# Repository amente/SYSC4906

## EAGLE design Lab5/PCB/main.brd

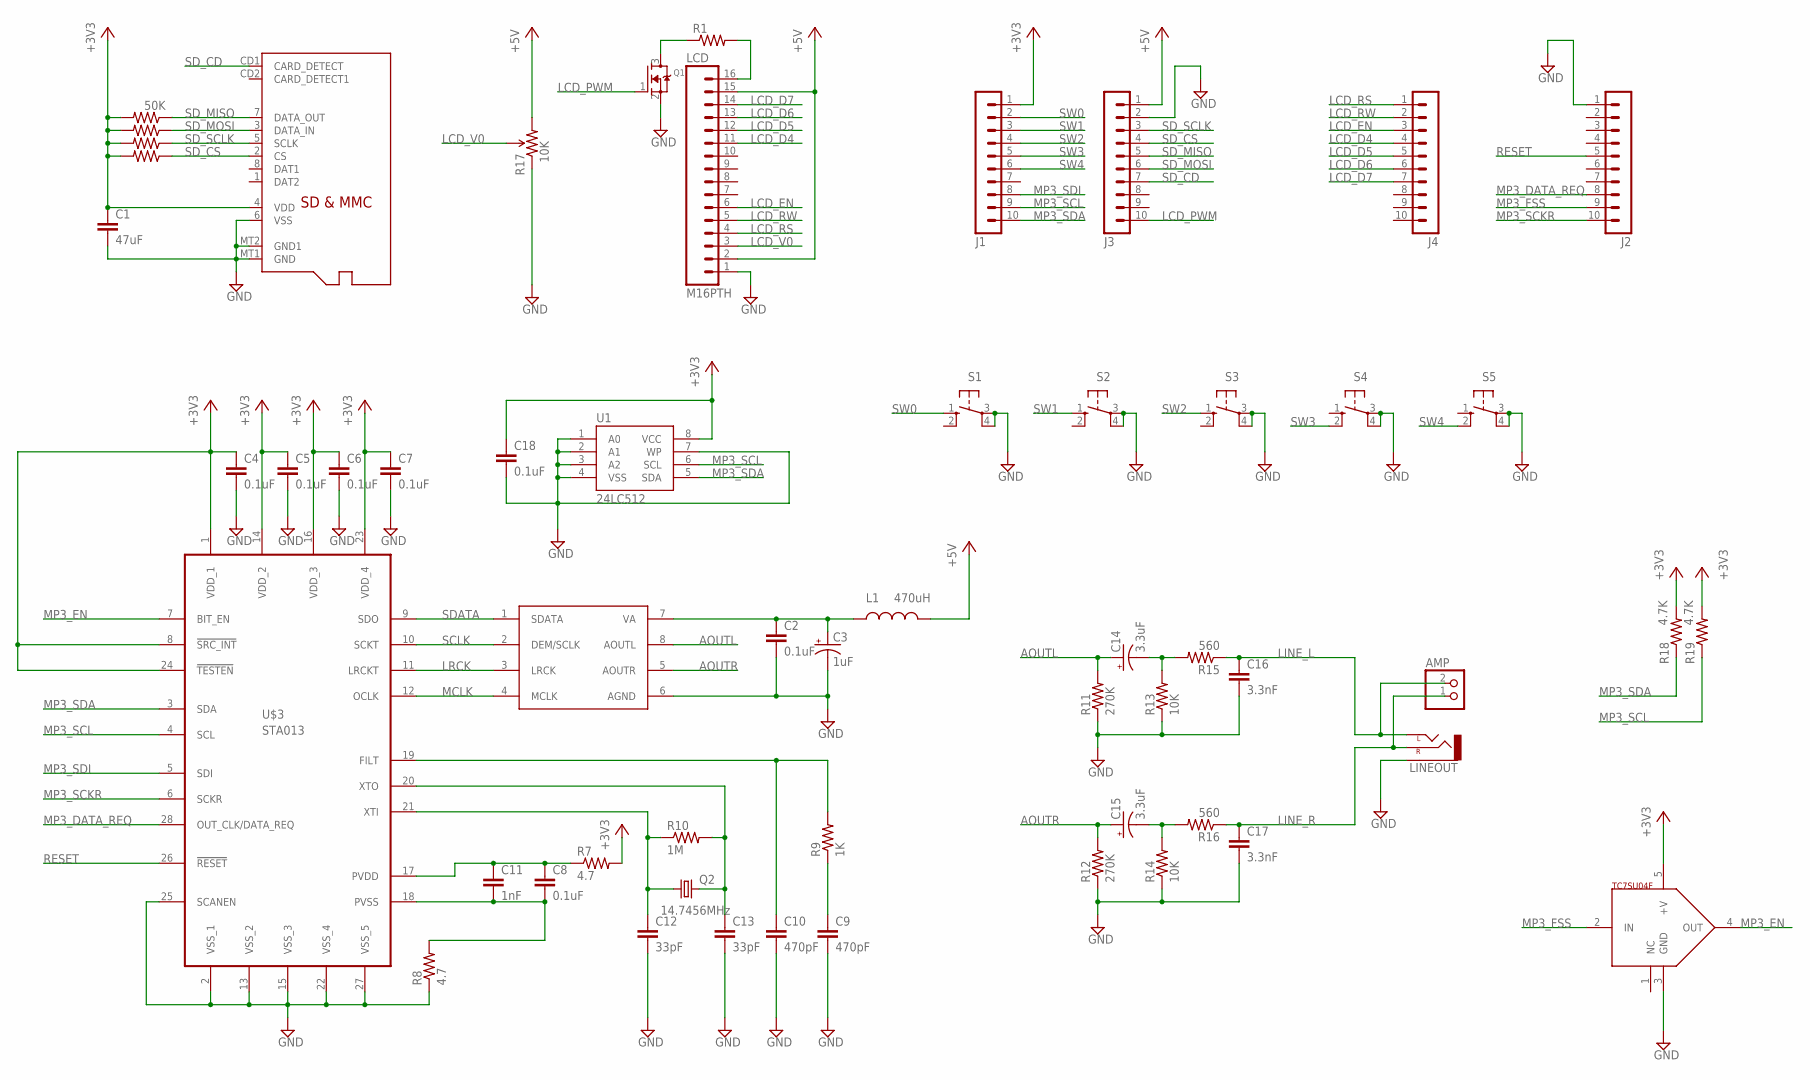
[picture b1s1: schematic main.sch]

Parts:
AMP: JST_2PIN-THM-RA; JST-PH-2-THM-RA
C1: 47uF; 0805
C2, C4, C5, C6, C7, C8, C18: 0.1uF; 0805
C3: 1uF; EIA3216
C9, C10: 470pF; 0805
C11: 1nF; 0805
C12, C13: 33pF; 0805
C14, C15: 3.3uF; EIA3216
C16, C17: 3.3nF; 0805
J1, J2, J3, J4: MA10-1; HEADER-10
L1: 470uH; SRR7032
LCD: M16PTH; 1X16
LINEOUT: AUDIO-JACKPTH; AUDIO-JACK
Q1: MOSFET-NREFLOW; SOT23
Q2: 14.7456MHz; HC49UP
R1: R-US_R0805; R0805
R3, R4, R5, R6: 50K; R0805
R7, R8: 4.7; R0805
R9: 1K; R0805
R10: 1M; R0805
R11, R12: 270K; R0805
R13, R14: 10K; R0805
R15, R16: 560; R0805
R17: 10K; 3364W
R18, R19: 4.7K; R0805
S1, S2, S3, S4, S5: 10-XX; B3F-10XX
U1: 24LC512; SO08
U$1: MICROSD
U$2: CS4334; SO08
U$3: STA013; SO28W
U$4: TC7SU04F; SOT23-5

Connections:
+3V3: C1.1, C4.1, C5.1, C6.1, C7.1, C18.1, J1.1, R3.2, R4.2, R5.2, R6.2, R7.2, R18.2, R19.2, U1.8 (VCC), U$1.4 (VDD), U$3.1 (VDD_1), U$3.8 (!SRC_INT), U$3.14 (VDD_2), U$3.16 (VDD_3), U$3.23 (VDD_4), U$3.24 (!TESTEN), U$4.5 (+V)
+5V: J3.1, L1.P$2 (2), LCD.2, LCD.15, R17.3 (CW)
AOUTL: C14.A (+), R11.2, U$2.8 (AOUTL)
AOUTR: C15.A (+), R12.2, U$2.5 (AOUTR)
GND: C1.2, C2.2, C3.C (-), C4.2, C5.2, C6.2, C7.2, C9.2, C10.2, C12.2, C13.2, C16.2, C17.2, C18.2, J2.1, J3.2, LCD.1, LINEOUT.SLEEVE, Q1.2 (S), R8.1, R11.1, R12.1, R13.1, R14.1, R17.1 (CCW), S1.3, S1.4 (P1), S2.3, S2.4 (P1), S3.3, S3.4 (P1), S4.3, S4.4 (P1), S5.3, S5.4 (P1), U1.1 (A0), U1.2 (A1), U1.3 (A2), U1.4 (VSS), U1.7 (WP), U$1.6 (VSS), U$1.MT1 (GND), U$1.MT2 (GND1), U$2.6 (AGND), U$3.2 (VSS_1), U$3.13 (VSS_2), U$3.15 (VSS_3), U$3.22 (VSS_4), U$3.25 (SCANEN), U$3.27 (VSS_5), U$4.3 (GND)
LCD_D4: J4.4, LCD.11
LCD_D5: J4.5, LCD.12
LCD_D6: J4.6, LCD.13
LCD_D7: J4.7, LCD.14
LCD_EN: J4.3, LCD.6
LCD_PWM: J3.10, Q1.1 (G)
LCD_RS: J4.1, LCD.4
LCD_RW: J4.2, LCD.5
LCD_V0: LCD.3, R17.2 (WIPER)
LINE_L: AMP.2 (1), C16.1, LINEOUT.TIP (LEFT), R15.1
LINE_R: AMP.1 (2), C17.1, LINEOUT.RING (RIGHT), R16.1
LRCK: U$2.3 (LRCK), U$3.11 (LRCKT)
MCLK: U$2.4 (MCLK), U$3.12 (OCLK)
MP3_DATA_REQ: J2.8, U$3.28 (OUT_CLK/DATA_REQ)
MP3_EN: U$3.7 (BIT_EN), U$4.4 (OUT)
MP3_FSS: J2.9, U$4.2 (IN)
MP3_SCKR: J2.10, U$3.6 (SCKR)
MP3_SCL: J1.9, R19.1, U1.6 (SCL), U$3.4 (SCL)
MP3_SDA: J1.10, R18.1, U1.5 (SDA), U$3.3 (SDA)
MP3_SDI: J1.8, U$3.5 (SDI)
unnamed: LCD.16, R1.2
unnamed: Q1.3 (D), R1.1
unnamed: C8.2, C11.2, R8.2, U$3.18 (PVSS)
unnamed: C8.1, C11.1, R7.1, U$3.17 (PVDD)
unnamed: C12.1, Q2.1, R10.1, U$3.21 (XTI)
unnamed: C13.1, Q2.2, R10.2, U$3.20 (XTO)
unnamed: C10.1, R9.2, U$3.19 (FILT)
unnamed: C9.1, R9.1
unnamed: C2.1, C3.A (+), L1.P$1 (1), U$2.7 (VA)
unnamed: C14.C (-), R13.2, R15.2
unnamed: C15.C (-), R14.2, R16.2
RESET: J2.5, U$3.26 (!RESET)
SCLK: U$2.2 (DEM/SCLK), U$3.10 (SCKT)
SDATA: U$2.1 (SDATA), U$3.9 (SDO)
SD_CD: J3.7, U$1.CD1 (CARD_DETECT)
SD_CS: J3.4, R6.1, U$1.2 (CS)
SD_MISO: J3.5, R3.1, U$1.7 (DATA_OUT)
SD_MOSI: J3.6, R4.1, U$1.3 (DATA_IN)
SD_SCLK: J3.3, R5.1, U$1.5 (SCLK)
SW0: J1.2, S1.1 (S)
SW1: J1.3, S2.1 (S)
SW2: J1.4, S3.1 (S)
SW3: J1.5, S4.2 (S1)
SW4: J1.6, S5.2 (S1)

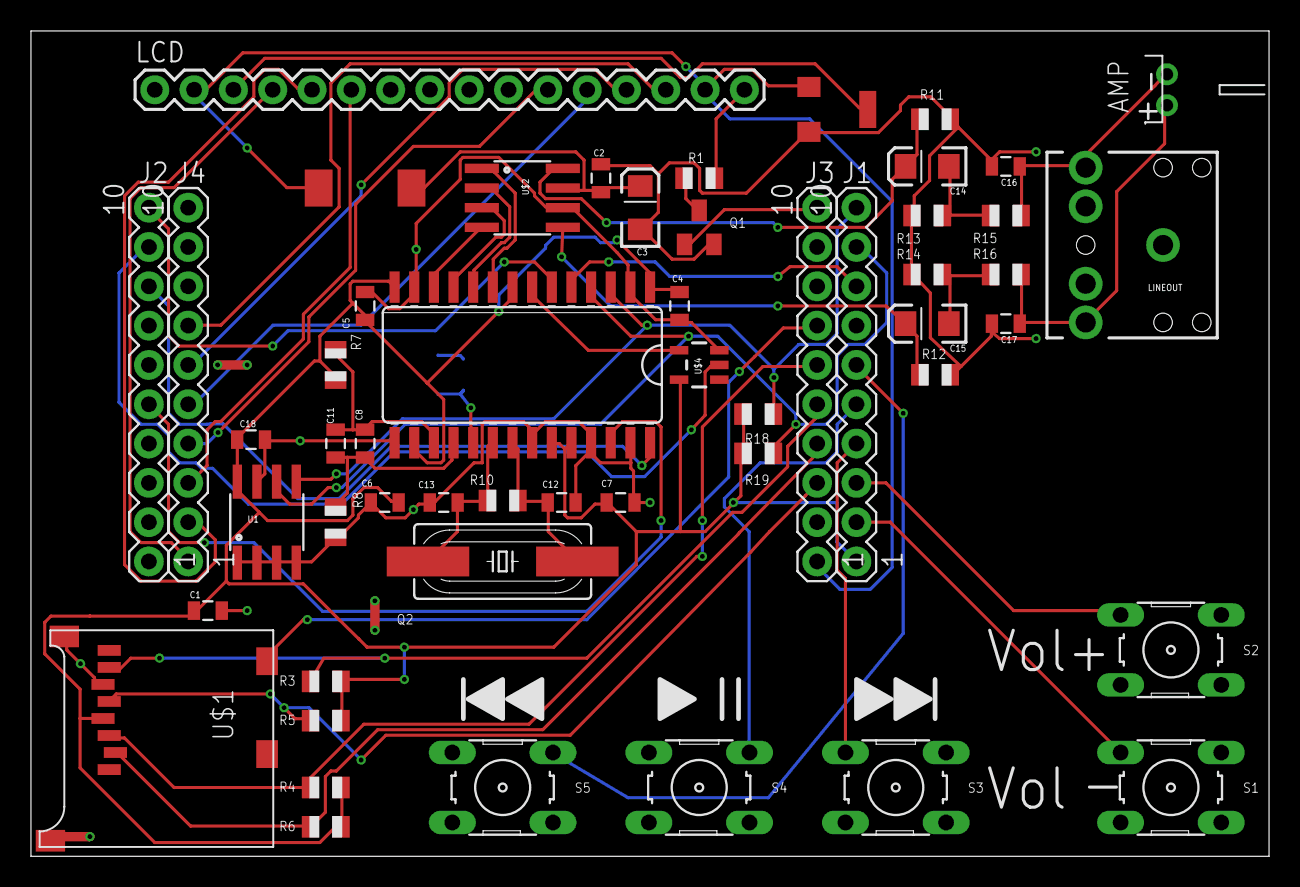
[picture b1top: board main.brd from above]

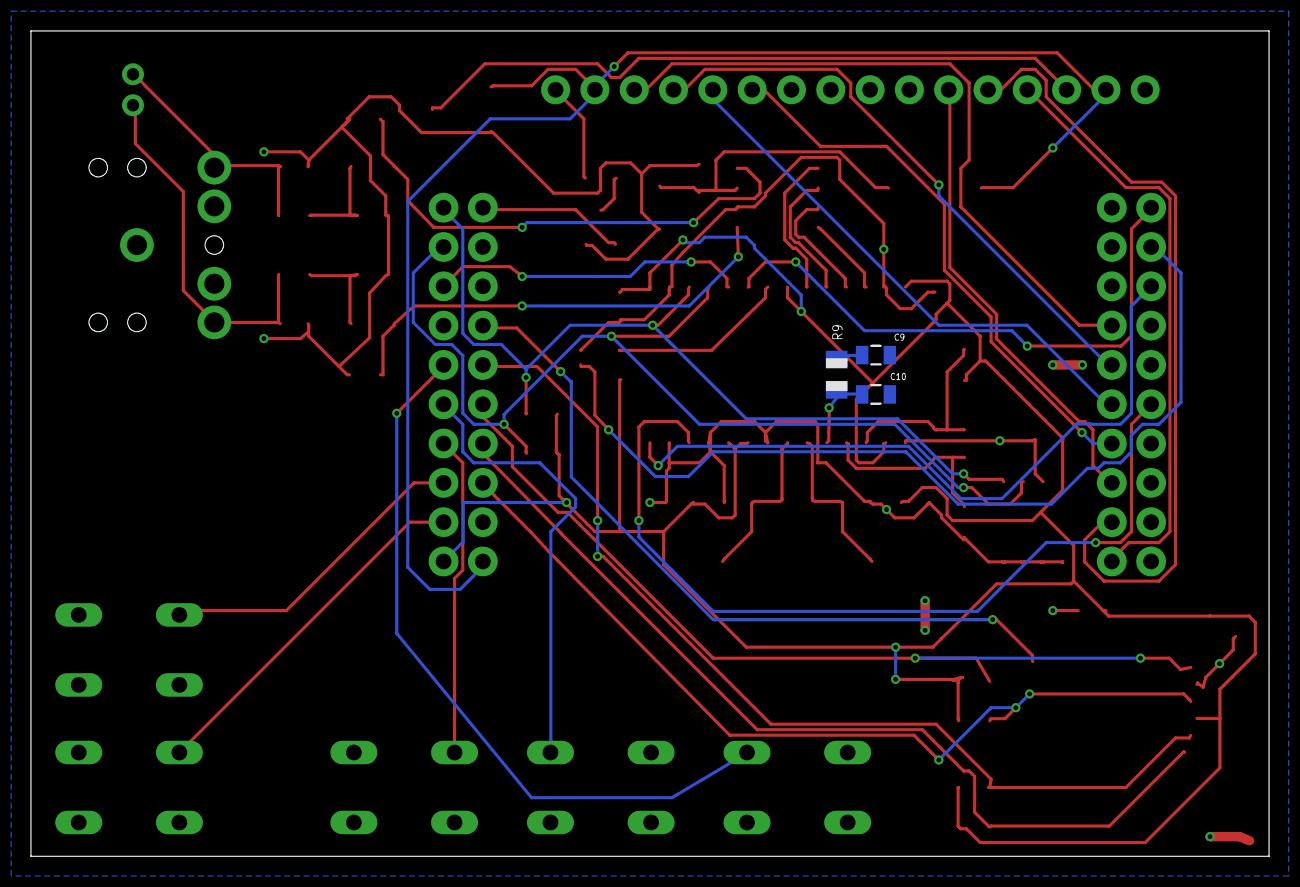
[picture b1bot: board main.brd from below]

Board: 2 copper layers, 80.0 x 53.3 mm, 56 parts (3 on the bottom side), 49 nets.

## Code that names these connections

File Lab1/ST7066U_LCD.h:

#include "CU_TM4C123.h"
#include <stdint.h>

#define LCD_DDRAM_LINE1_ADDR 0x80
#define LCD_DDRAM_LINE2_ADDR 0xC0

#define LCD_CONTROL_PORT       GPIOE
#define LCD_CONTROL_PORT_RCGC  (1UL<<4)
#define LCD_CONTROL_RS_PIN     (1UL<<1)
#define LCD_CONTROL_RW_PIN     (1UL<<2)
#define LCD_CONTROL_EN_PIN     (1UL<<3)

#define LCD_DATA_PORT          GPIOB
#define LCD_DATA_PORT_RCGC     (1UL<<1)

#define LCD_RW(x)   ((x) ?(LCD_CONTROL_PORT->DATA |= 0x04):(LCD_CONTROL_PORT->DATA &= ~0x04))
#define LCD_RS(x)   ((x) ?(LCD_CONTROL_PORT->DATA |= 0x02):(LCD_CONTROL_PORT->DATA &= ~0x02))
#define LCD_EN(x)   ((x) ?(LCD_CONTROL_PORT->DATA |= 0x08):(LCD_CONTROL_PORT->DATA &= ~0x08))

#define RS_ADDR	0
#define RS_DATA	1

#define LCD_write(RS,data)   				__LCD_write(RS,data,1)
#define LCD_write_no_wait(RS,data)	__LCD_write(RS,data,0)

void __LCD_write(uint8_t RS,uint8_t data,uint8_t wait);
uint8_t LCD_read(uint8_t RS);
void LCD_init(void);
void LCD_write_str(char *str,uint8_t pos);
void LCD_write_nstr(char *str, uint8_t n, uint8_t pos);

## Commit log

2014-09-14 Added gitignore
2014-09-14 Initial commit LCD works
2014-09-17 Implemented Backlight PWM
2014-09-23 Ignoring the test dir and pdf files
2014-09-24 Finished Lab1 and ready to demo
2014-10-08 Converted tabs to 4 spaces
2014-10-08 Initial commit of Lab2; Ready to demo
2014-10-28 Working Lab3 init commit
2014-10-28 UART init commit
2014-10-28 Working UART chat client code
2014-11-20 Init commit for Lab4. Ready to demo
2014-11-28 Updated UART code
2014-11-28 Misc cleanup
2014-11-28 Init commit of Lab 5. Ready to demo
2014-11-28 Added continuous playing but there's a bug when the player has reach the last song
2014-11-30 Refactor and comments of gui.c
2014-12-01 Implemented screen dimming. All button codes are in ISRs. Fixed bug when the player reaches the last song.
2014-12-01 Fixed a regression
2014-12-02 Fixed a bug in the LCD read code that could cause the BF poll to hang
2014-12-02 Fixed behavior of LCD_write_nstr
2014-12-02 Changed Fatfs back to non-reentrant and allocate LFN on BSS because of its weird use of dynamic memory
2014-12-02 Fixed filetype detection, refactored display code, implemented song count
2014-12-06 Implemented song name centering and file size display
2014-12-06 Increased stack size for GUI thread so snprintf can handle floating points
2014-12-07 Added LCD_write_nstr_f to force write the specified num of chars
2014-12-07 Added spin animation and reformatted the LCD layout
2014-12-07 Implemented volume display
2014-12-07 Added volume display Mute
2014-12-07 Implemented Card Detect
2014-12-07 Fixed a bug where the null term char was not accounted for when allocating the song linked list
2014-12-08 Implemented long song name scrolling
2014-12-08 Added extra delays for title scrolling
2014-12-08 Init commit of PCB

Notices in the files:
parts and their libraries:
SparkFun-Capacitors: Licensing: Creative Commons ShareAlike 4.0 International - https://creativecommons.org/licenses/by-sa/4.0
